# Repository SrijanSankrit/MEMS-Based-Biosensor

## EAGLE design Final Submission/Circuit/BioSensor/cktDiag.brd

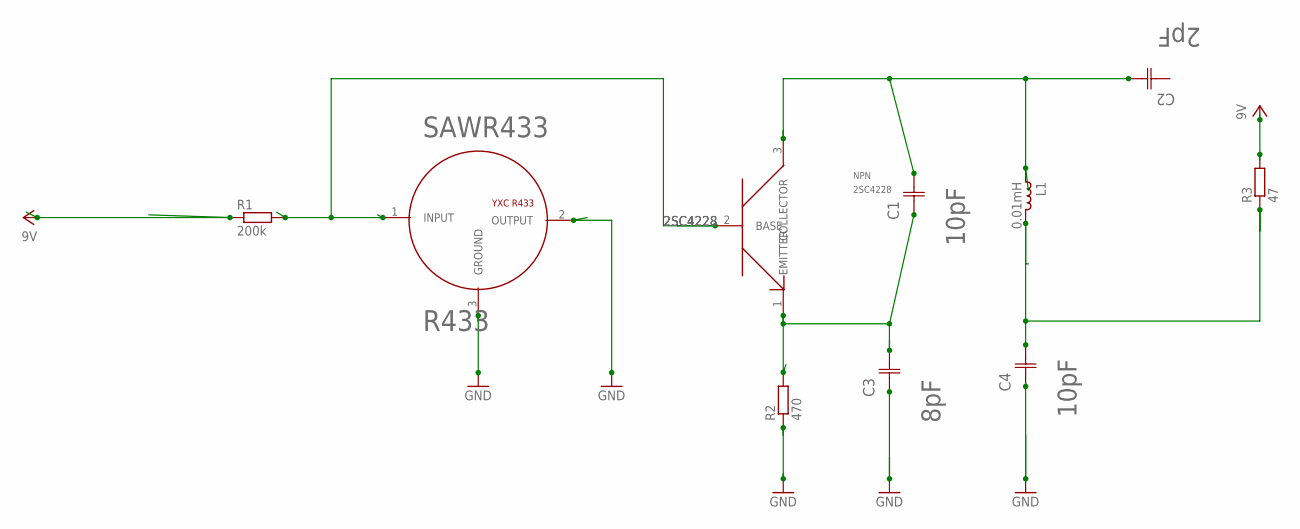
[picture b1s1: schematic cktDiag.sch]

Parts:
C1, C4: 10pF; CAPC1608X85N
C2: 2pF; CAPC1608X85N
C3: 8pF; CAPC1608X85N
L1: 0.01mH; L0603
NPN: 2SC4228
R1: 200k; R0603
R2: 470; R0603
R3: 47; R0603
SAWR433: R433; RX33

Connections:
2SC4228: NPN.2 (BASE), R1.2, SAWR433.1 (INPUT)
GND: C3.1 (C1), C4.1 (C1), R2.1, SAWR433.2 (OUTPUT), SAWR433.3 (GROUND)
unnamed: C1.1 (C1), C3.2 (C2), NPN.1 (EMITTER), R2.2
unnamed: C1.2 (C2), C2.2 (C2), L1.2, NPN.3 (COLLECTOR)
unnamed: C4.2 (C2), L1.1, R3.1
VCC: R1.1, R3.2

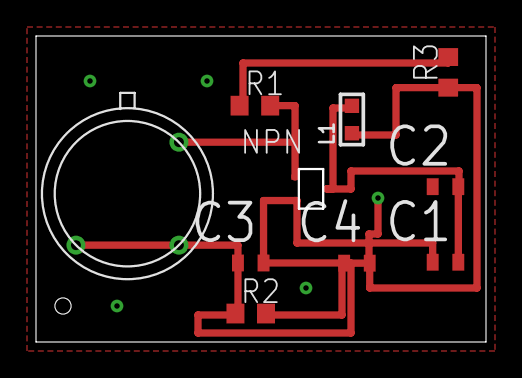
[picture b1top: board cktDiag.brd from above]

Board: 2 copper layers, 24.9 x 16.9 mm, 10 parts (0 on the bottom side), 6 nets.

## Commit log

2020-08-11 initialCommit

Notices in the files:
parts and their libraries:
rc-master-smd: Copyright (C) 2007, Bob Starr
